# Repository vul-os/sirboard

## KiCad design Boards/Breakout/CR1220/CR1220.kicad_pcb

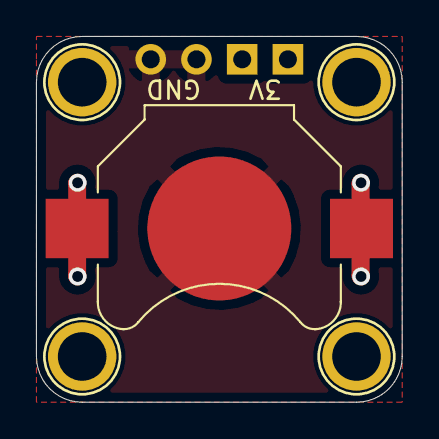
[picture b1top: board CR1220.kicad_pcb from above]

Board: 2 copper layers, 20.3 x 20.3 mm, 6 parts (0 on the bottom side), 2 nets.

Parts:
BT1: Battery_Cell; BatteryHolder_Keystone_3000_1x12mm
H1, H2, H3, H4: MountingHole; MountingHole_M2.5_SirBoard
J1: Conn_01x04; PinHeader_1x04_P2.54mm_Vertical

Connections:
+3V0: BT1.1, J1.1, J1.2
GND: BT1.2, J1.3, J1.4

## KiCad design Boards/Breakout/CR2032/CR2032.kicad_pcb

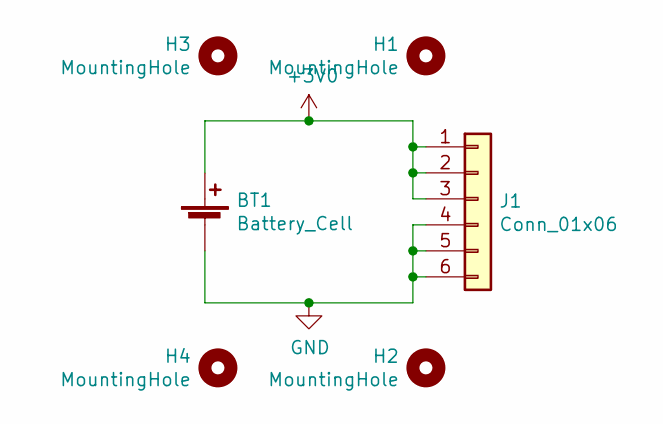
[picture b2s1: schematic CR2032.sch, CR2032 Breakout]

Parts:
BT1: Battery_Cell; BatteryHolder_Keystone_3008_1x2450; Part C238100
H1, H2, H3, H4: MountingHole; MountingHole_M2.5_SirBoard
J1: Conn_01x06; PinHeader_1x06_P2.54mm_Vertical

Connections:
+3V0: BT1.1 (+), J1.1, J1.2, J1.3
GND: BT1.2 (-), J1.4, J1.5, J1.6

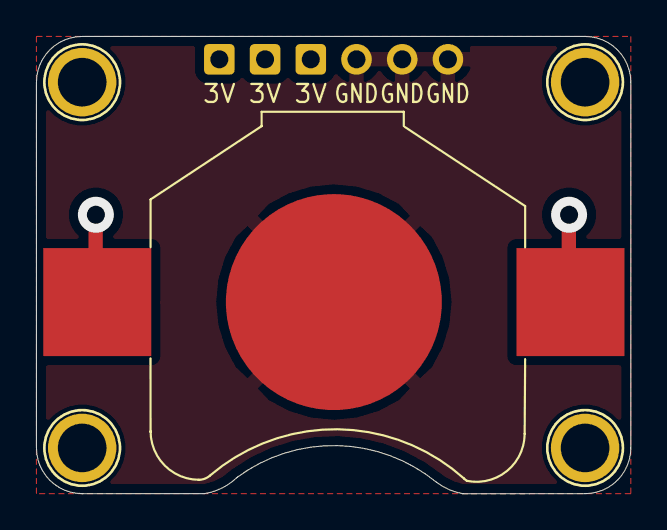
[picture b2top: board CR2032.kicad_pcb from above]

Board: 2 copper layers, 33.0 x 25.4 mm, 6 parts (0 on the bottom side), 2 nets.

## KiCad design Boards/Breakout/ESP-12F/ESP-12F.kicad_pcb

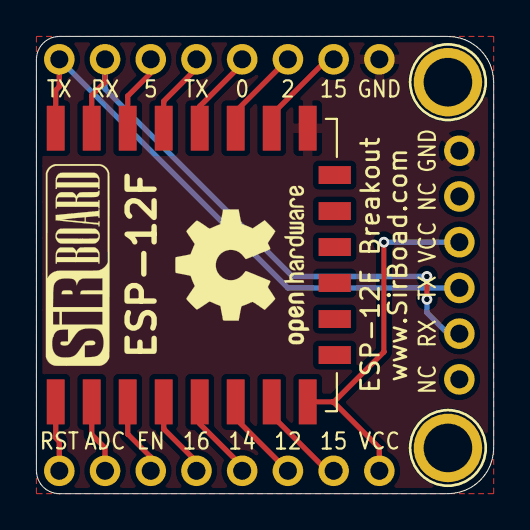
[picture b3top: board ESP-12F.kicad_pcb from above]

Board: 2 copper layers, 25.4 x 25.4 mm, 6 parts (0 on the bottom side), 16 nets.

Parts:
ESP-12F: ESP-12F; ESP-12E
H2, H4: MountingHole; MountingHole_M2.5_SirBoard
J1, J2: Conn_01x08; PinHeader_1x08_P2.54mm_Vertical
J3: Conn_01x06; PinHeader_1x06_P2.54mm_Horizontal

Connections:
ADC: ESP-12F.2, J1.2
EN: ESP-12F.3, J1.3
GND: ESP-12F.15, J2.8, J3.1
GPI16: ESP-12F.4, J1.4
GPIO0: ESP-12F.18, J2.5
GPIO2: ESP-12F.17, J2.6
GPIO4: ESP-12F.19, J2.4
GPIO5: ESP-12F.20, J2.3
GPIO12: ESP-12F.6, J1.6
GPIO13: ESP-12F.7, J1.7
GPIO14: ESP-12F.5, J1.5
GPIO15: ESP-12F.16, J2.7
RST: ESP-12F.1, J1.1
RX: ESP-12F.21, J2.2, J3.5
TXD: ESP-12F.22, J2.1, J3.4
VCC: ESP-12F.8, J1.8, J3.3

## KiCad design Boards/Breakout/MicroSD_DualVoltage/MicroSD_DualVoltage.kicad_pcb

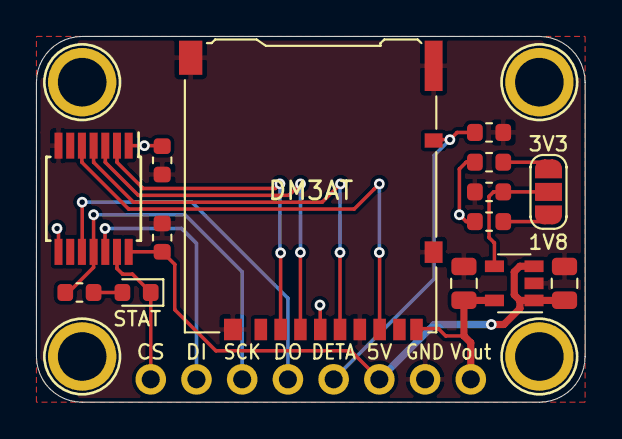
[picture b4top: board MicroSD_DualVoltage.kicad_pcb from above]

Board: 2 copper layers, 30.5 x 20.3 mm, 19 parts (1 on the bottom side), 16 nets.

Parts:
C1, C2: 10uF; C_0805_2012Metric
C3, C4: 100nF; C_0603_1608Metric
DM3AT: Micro_SD_Card_Det; microSD_HC_Hirose_DM3AT-SF-PEJM5
H1, H2, H3, H4: MountingHole; MountingHole_M2.5_SirBoard
J1: Conn_01x08; PinHeader_1x08_P2.54mm_Vertical
JP1: SolderJumper_3_Open; SolderJumper-3_P1.3mm_Open_RoundedPad1.0x1.5mm
R1: 31K6; R_0603_1608Metric
R2: 12K4; R_0603_1608Metric
R3, R4: 10K; R_0603_1608Metric
R6: 1K; R_0603_1608Metric
STAT: LED; LED_0603_1608Metric
U1: AP7365; SOT-23-5
U2: TXB0104PW; TSSOP-14_4.4x5mm_P0.65mm

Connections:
/CLK_SD: DM3AT.5, U2.4
/CS_SD: DM3AT.2, U2.2
/DI_SD: DM3AT.3, U2.3
/DO_SD: DM3AT.7, U2.5
ADJ: JP1.2, R3.1, U1.4
CS: J1.1, STAT.1, U2.13
DETA: DM3AT.10, J1.5, R4.1
DI: J1.2, U2.12
DO: J1.4, U2.10
GND: C1.2, C2.2, C3.2, C4.2, DM3AT.6, DM3AT.11, J1.7, R3.2, R4.2, U1.2, U2.7
unnamed: R6.2, STAT.2
unnamed: JP1.1, R1.2
unnamed: JP1.3, R2.2
SCK: J1.3, R6.1, U2.11
VIN: C1.1, C3.1, J1.6, U1.1, U1.3, U2.14
VOUT: C2.1, C4.1, DM3AT.4, DM3AT.9, J1.8, R1.1, R2.1, U1.5, U2.1, U2.8

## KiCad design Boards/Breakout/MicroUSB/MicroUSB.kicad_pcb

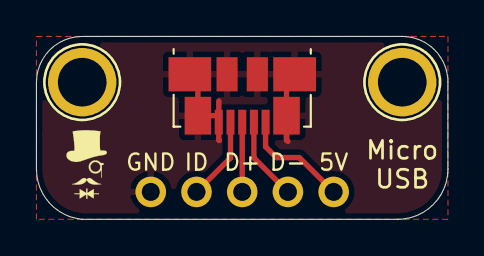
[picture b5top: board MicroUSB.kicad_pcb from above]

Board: 2 copper layers, 22.9 x 10.2 mm, 4 parts (1 on the bottom side), 5 nets.

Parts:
H1, H2: MountingHole; MountingHole_M2.5_SirBoard
J1: USB_B_Micro; USB_Micro-B_Molex_47346-0001
J2: Conn_01x05; PinHeader_1x05_P2.54mm_Vertical

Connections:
/D+: J1.3, J2.3
/D-: J1.2, J2.2
/GND: J1.5, J1.6, J2.5
/ID: J1.4, J2.4
/VBus: J1.1, J2.1

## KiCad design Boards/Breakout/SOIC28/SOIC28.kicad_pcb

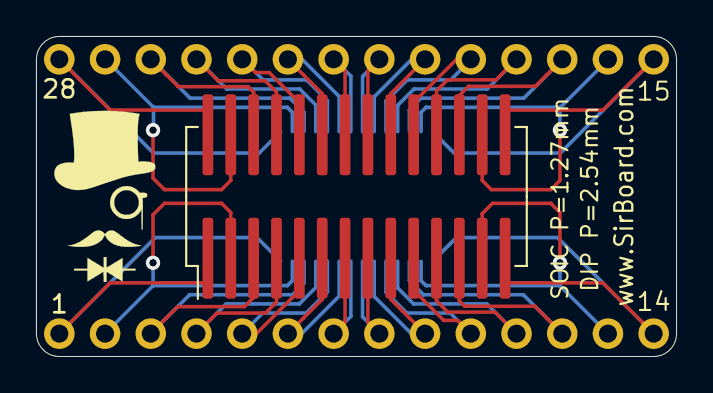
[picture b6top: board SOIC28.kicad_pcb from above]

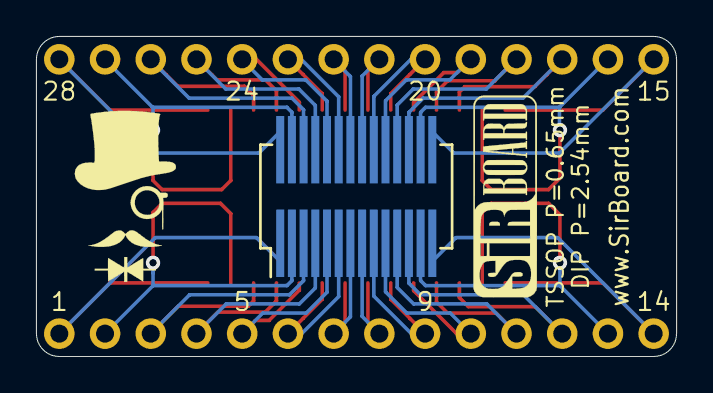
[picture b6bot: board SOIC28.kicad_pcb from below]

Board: 2 copper layers, 35.6 x 17.8 mm, 4 parts (3 on the bottom side), 28 nets.

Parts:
J1, J3: Conn_01x14; PinHeader_1x14_P2.54mm_Vertical
J2: Conn_02x14_Counter_Clockwise; SOIC-28W_7.5x18.7mm_P1.27mm
J4: Conn_02x14_Counter_Clockwise; SSOP-28_5.3x10.2mm_P0.65mm

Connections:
unnamed: J1.1, J2.1, J4.14
unnamed: J1.2, J2.2, J4.13
unnamed: J1.3, J2.3, J4.12
unnamed: J1.4, J2.4, J4.11
unnamed: J1.5, J2.5, J4.10
unnamed: J1.6, J2.6, J4.9
unnamed: J1.7, J2.7, J4.8
unnamed: J1.8, J2.8, J4.7
unnamed: J1.9, J2.9, J4.6
unnamed: J1.10, J2.10, J4.5
unnamed: J1.11, J2.11, J4.4
unnamed: J1.12, J2.12, J4.3
unnamed: J1.13, J2.13, J4.2
unnamed: J1.14, J2.14, J4.1
unnamed: J2.15, J3.14, J4.28
unnamed: J2.16, J3.13, J4.27
unnamed: J2.17, J3.12, J4.26
unnamed: J2.18, J3.11, J4.25
unnamed: J2.19, J3.10, J4.24
unnamed: J2.20, J3.9, J4.23
unnamed: J2.21, J3.8, J4.22
unnamed: J2.22, J3.7, J4.21
unnamed: J2.23, J3.6, J4.20
unnamed: J2.24, J3.5, J4.19
unnamed: J2.25, J3.4, J4.18
unnamed: J2.26, J3.3, J4.17
unnamed: J2.27, J3.2, J4.16
unnamed: J2.8, J3.1, J4.15

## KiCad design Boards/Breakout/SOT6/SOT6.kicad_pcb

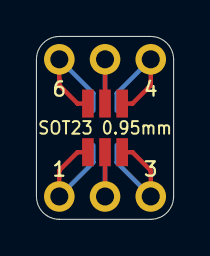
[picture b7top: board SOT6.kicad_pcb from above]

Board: 2 copper layers, 7.6 x 10.2 mm, 4 parts (1 on the bottom side), 6 nets.

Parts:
J1, J2: Conn_01x03; PinHeader_1x03_P2.54mm_Vertical
J3: Conn_02x03_Counter_Clockwise; SOT-23-6_Handsoldering
J4: Conn_02x03_Counter_Clockwise; SOT-363_SC-70-6_Handsoldering

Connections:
unnamed: J1.1, J3.6, J4.1
unnamed: J1.2, J3.5, J4.2
unnamed: J1.3, J3.4, J4.3
unnamed: J2.1, J3.1, J4.6
unnamed: J2.2, J3.2, J4.5
unnamed: J2.3, J3.3, J4.4
